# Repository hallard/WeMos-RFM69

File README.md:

ESP8266 WeMos Shield for HopeRF RFM69 and RFM12 Modules
=======================================================

This shield is used to hold HopeRF RF [module][4] Software with WeMos ESP8266 boards it has just few minimal features. 
- I2C Pullups placement
- Classic I2C 128x64 OLED connector
- Placement for RFM12B/RFM69CW/RFM69W/RFM69HW RF module
- Placement for choosing single Wire, SMA or u-FL Antenna type
- 2 x WS2812B Type LED for visual indication
- Atmel ATSHA204 for crypto
- Custom switch on GPIO2

You can find more information on WeMos on their [site][1], it's really well documented.
I now use WeMos boards instead of NodeMCU's one because they're just smaller, features remains the same, but I also suspect WeMos regulator far better quality than the one used on NodeMCU that are just fake of originals AMS117 3V3.

Boards heve been tested with RFM69HW and are working fine, no problem so far, just a silk error on V1.0, RFM module indication is reversed.
This mean that RFM69W/RFM69HW is for RFM12B/RFM69CW and vice-versa, please check with module pinout before soldering.
**This have been corrected on V1.0a+ release**

**I didn't tested with RFM12/RFM69CW module.** If someone tested and have it working (or not), please let me know.

Detailed Description
====================

Look at the schematics for more informations.

### Schematic  

Diode D1 (1N4148) is for level voltage of WS2812B. Decreasing 1st led to VCC to 4.3V (see this [post][5]) but It should works out of the box (so without D1 and JP4 closed) without any problem. 
Depending on WS2812 type, if it does not work or flicker, open JP4 (cut wire) and put D1 in place.

### Boards  
&nbsp;

You can order the PCB of this board at [PBCs.io][3], if you do so, PCBs.io give me little discount that allow me to buy some new created boards.

### Assembled boards

All assembled boards are working fine.

## License

This work is licensed under a [Creative Commons Attribution-NonCommercial 4.0 International License](http://creativecommons.org/licenses/by-nc/4.0/)    
If you want to do commercial stuff with this project, please contact [CH2i company](https://www.ch2i.eu/en#support) so we can organize an simple agreement.

## Misc
See news and other projects on my [blog][2] 
 
[1]: http://www.wemos.cc/wiki/doku.php?id=en:d1_mini
[2]: https://hallard.me
[3]: https://PCBs.io/share/8Vkkr 
[4]: http://www.hoperf.com/rf_transceiver/modules/
[5]: http://www.electrobob.com/ws2812-level-translator/

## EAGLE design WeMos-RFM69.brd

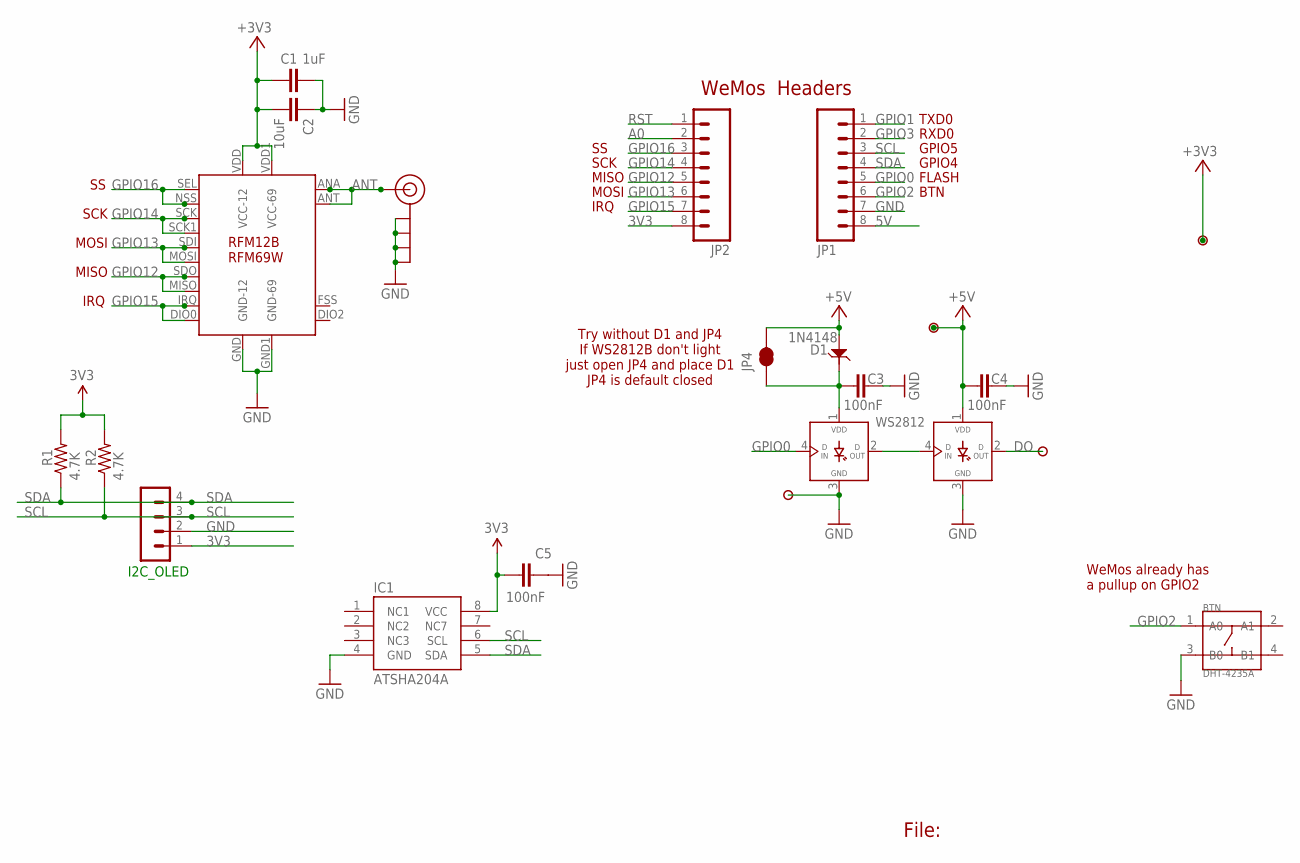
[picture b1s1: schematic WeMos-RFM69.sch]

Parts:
BTN: DHT-4235A; SW4-SMD-4.2X3.2X2.5MM
C1: 1uF; 0805-CAP-LARGEPADS
C2: 10uF; 0805-CAP-LARGEPADS
C3, C4, C5: 100nF; 0805-CAP
D1: 1N4148; SOD123-2.7X1.6
I2C_OLED: CON_HEADER_1X04'LOCK'; 1X04_LOCK
IC1: ATSHA204A; SOIC8
J$1: ANTENNATINY; SMA_UFL_PAD_TINY
JP1, JP2: M08NO_SILK_FEMALE_PTH; 1X08_NO_SILK
JP4: JUMPER-PAD-2-NC_BY_TRACE; PAD-JUMPER-2-NC_BY_TRACE_YES_SILK
P1, P2, P3, P4: PADNORMAL; PAD
R1, R2: 4.7K; 0805-RES
U$1: RFM-DUAL
WS1, WS2812: WS2812B

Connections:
3V3: C1.2, C2.2, C5.2, I2C_OLED.1, IC1.8 (VCC), JP2.8, P4.1, R1.2, R2.2, U$1.VDD (VCC-12), U$1.VDD1 (VCC-69)
5V: C4.1, D1.1, JP1.8, JP4.2, P1.1, WS1.1 (VDD)
A0: JP2.2
ANT: J$1.ANT1 (SIGNAL), J$1.ANT2 (SIGNAL), J$1.ANT3 (SIGNAL), U$1.ANA (ANT-12), U$1.ANT (ANT-69)
DO: P2.1, WS1.2 (DOUT)
GND: BTN.3 (B0), C1.1, C2.1, C3.2, C4.2, C5.1, I2C_OLED.2, IC1.4 (GND), J$1.GND1 (GND), J$1.GND2 (GND), J$1.GND3 (GND), J$1.GND4 (GND), JP1.7, P3.1, U$1.GND (GND-12), U$1.GND1 (GND-69), WS1.3 (GND), WS2812.3 (GND)
GPIO0: JP1.5, WS2812.4 (DIN)
GPIO1: JP1.1
GPIO2: BTN.1 (A0), JP1.6
GPIO3: JP1.2
GPIO12: JP2.5, U$1.MISO, U$1.SDO
GPIO13: JP2.6, U$1.MOSI, U$1.SDI
GPIO14: JP2.4, U$1.SCK, U$1.SCK1
GPIO15: JP2.7, U$1.DIO0, U$1.IRQ
GPIO16: JP2.3, U$1.NSS (SEL-12), U$1.SEL (SEL-69)
unnamed: WS1.4 (DIN), WS2812.2 (DOUT)
RST: JP2.1
SCL: I2C_OLED.3, IC1.6 (SCL), JP1.3, R2.1
SDA: I2C_OLED.4, IC1.5 (SDA), JP1.4, R1.1
VLED: C3.1, D1.2, JP4.1, WS2812.1 (VDD)

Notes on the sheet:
File:
FLASH
MISO
GPIO4
GPIO5
RXD0
TXD0
MOSI
SCK
IRQ
WeMos Headers
WeMos already has a pullup on GPIO2
BTN
Try without D1 and JP4 If WS2812B don't light just open JP4 and place D1 JP4 is default closed

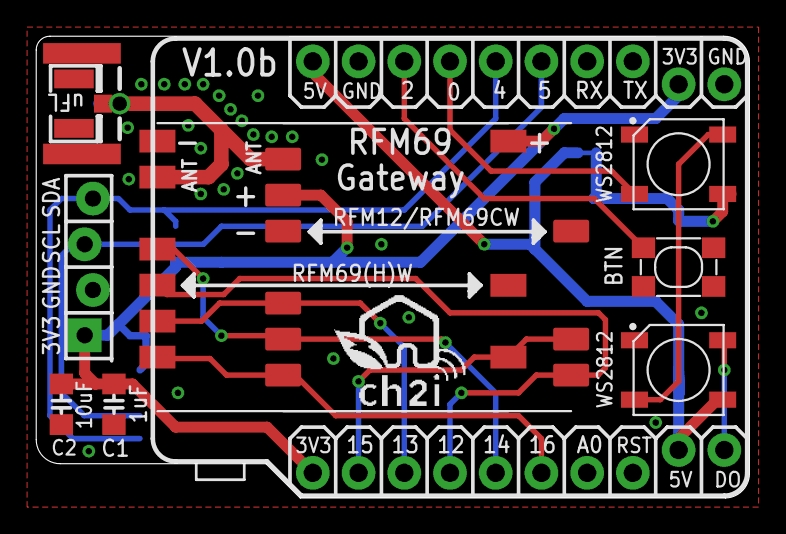
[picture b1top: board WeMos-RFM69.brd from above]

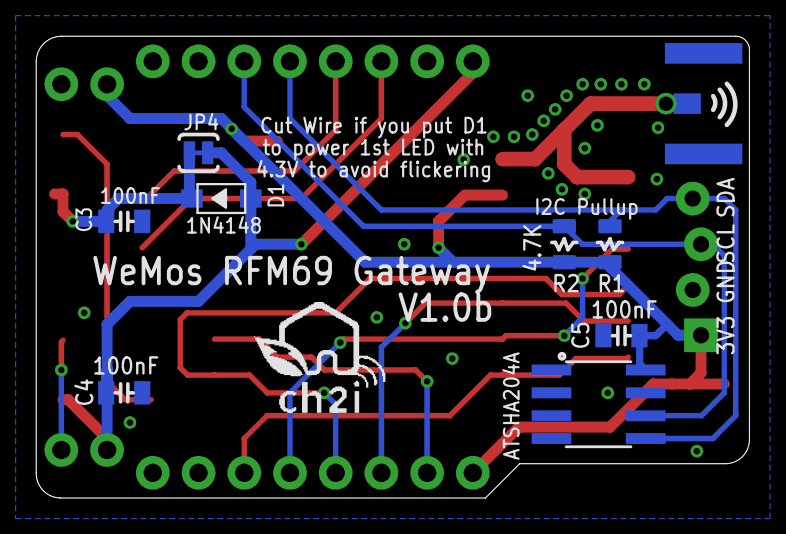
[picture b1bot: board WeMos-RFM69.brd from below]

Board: 2 copper layers, 39.6 x 25.7 mm, 24 parts (9 on the bottom side), 16 nets.

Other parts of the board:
U$2, U$4: LOGO_CH2I_75MM

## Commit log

2016-04-26 Creation
2016-04-26 Added OSH Park Link
2016-05-30 File was misnamed
2016-05-30 Version 1.0a
2016-05-30 Added V1.0a OSHPark link
2016-05-30 Added note about RFM12B test
2016-05-30 Better explanation on JP4 and D1
2016-07-07 Version 1.0b
    OLED Display connector has now lock pad
    Antenna signal with via
    ground plane set to 12min blocking to avoid short circuit with
    connectors
2016-07-07 Moved to pictures folder
2016-07-07 V1.0b description
2016-07-07 Not used bad format
2016-07-07 Picture from PCBs.io
2016-07-07 deleted svg pictures format
2016-07-07 bad link
2018-03-22 Added license

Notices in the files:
parts and their libraries:
SparkFun-Connectors: Licensing: Creative Commons ShareAlike 4.0 International - https://creativecommons.org/licenses/by-sa/4.0
